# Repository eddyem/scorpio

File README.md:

# scorpio
SCORPIO control system

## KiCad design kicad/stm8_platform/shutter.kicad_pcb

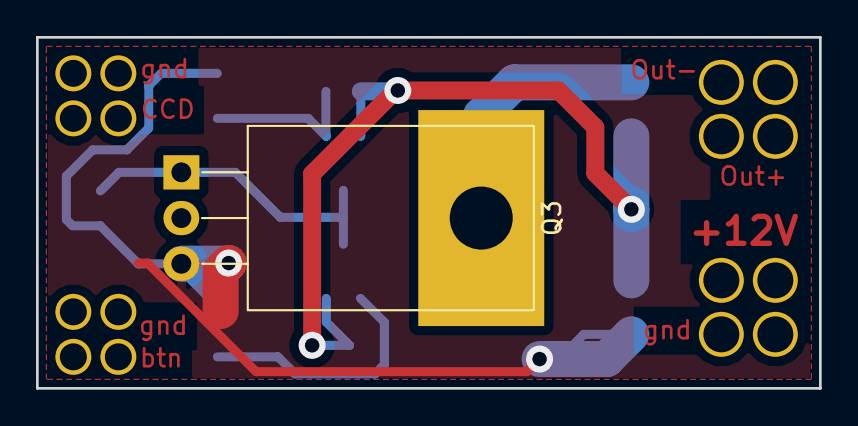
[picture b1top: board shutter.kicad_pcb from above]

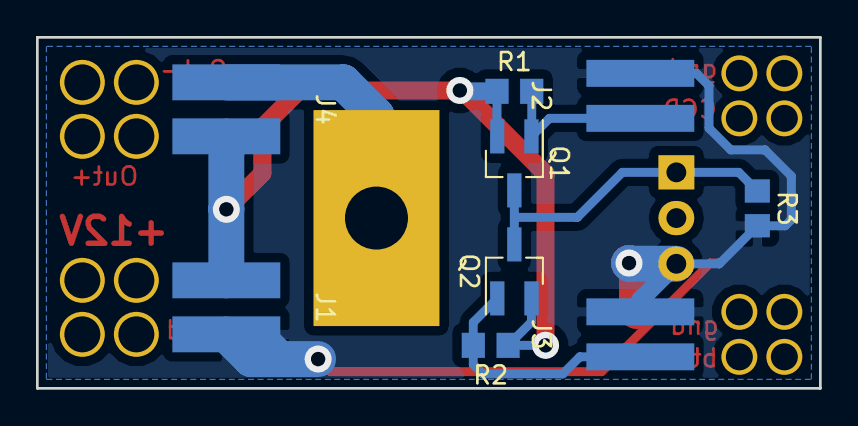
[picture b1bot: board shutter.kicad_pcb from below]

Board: 2 copper layers, 43.5 x 19.5 mm, 10 parts (9 on the bottom side), 6 nets.

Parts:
J1: Power; 2PIN_Pwr
J2: CCD; 2PIN
J3: Button; 2PIN
J4: Sutter; 2PIN_Pwr
Q1, Q2: AO3407; SOT-23_Handsoldering
Q3: IRL3303; TO-220-3_Horizontal_TabDown
R1, R2, R3: 47k; R_0805_2012Metric_Pad1.29x1.40mm_HandSolder

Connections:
+12V: J1.2, J4.1, Q1.2, Q2.2, R1.1, R2.1
GND: J1.1, J2.1, J3.1, Q3.3, R3.2
unnamed: J2.2, Q1.1, R1.2
unnamed: J3.2, Q2.1, R2.2
unnamed: J4.2, Q3.2
unnamed: Q1.3, Q2.3, Q3.1, R3.1

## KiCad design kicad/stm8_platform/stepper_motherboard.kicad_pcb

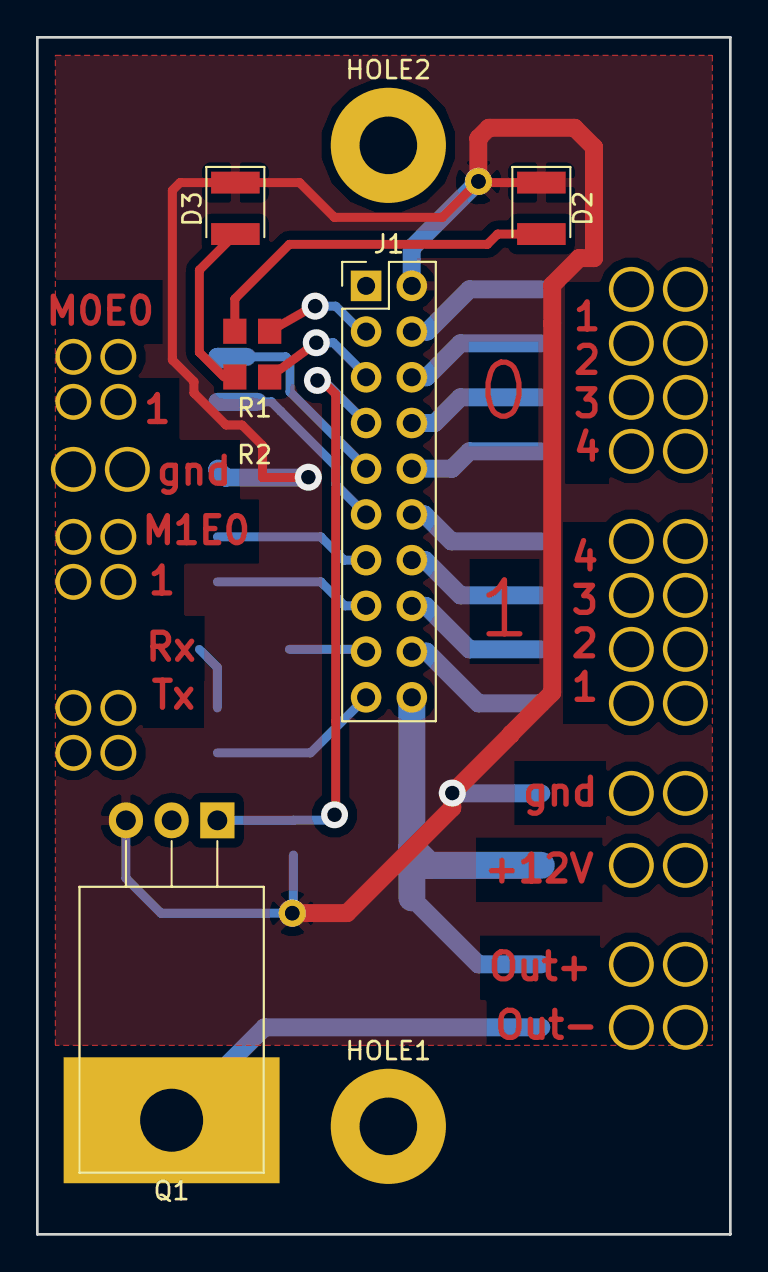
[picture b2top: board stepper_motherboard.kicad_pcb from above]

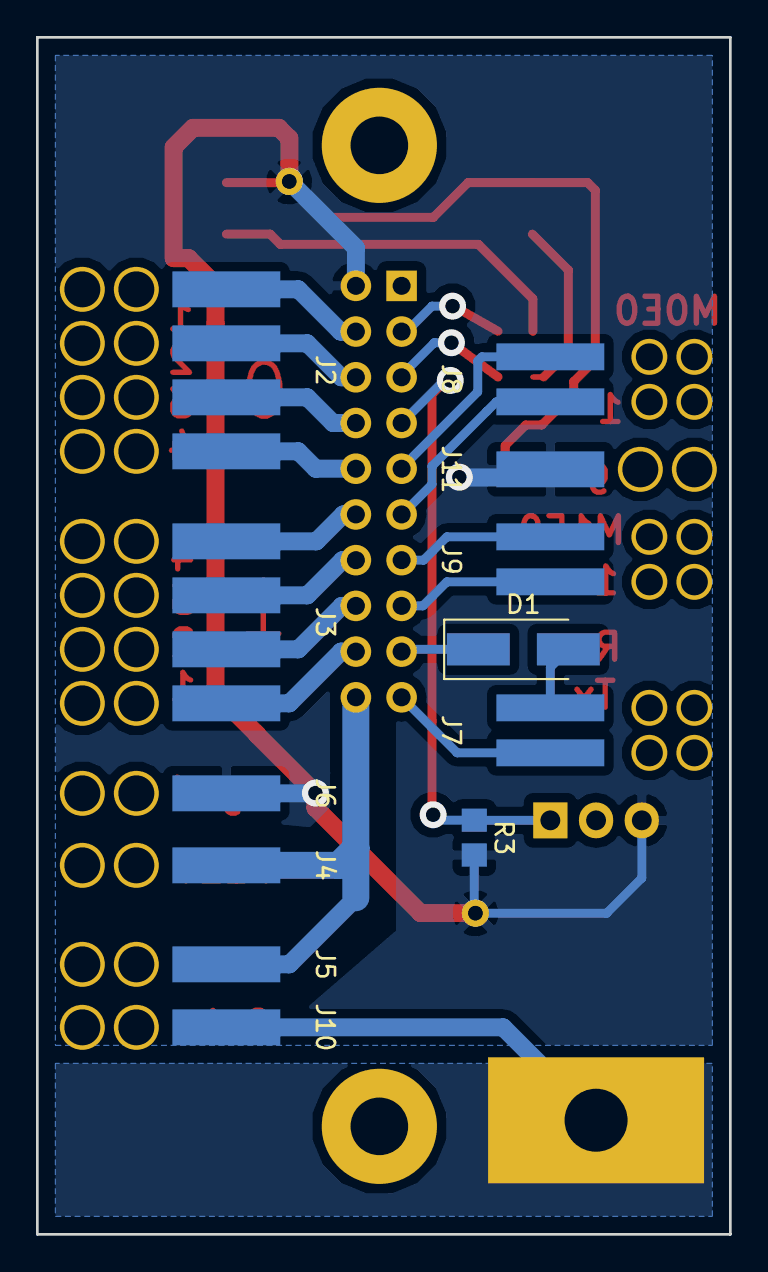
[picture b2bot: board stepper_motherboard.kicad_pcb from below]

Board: 2 copper layers, 38.5 x 66.5 mm, 20 parts (12 on the bottom side), 23 nets.

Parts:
D1: SS14; D_SMA_Handsoldering
D2, D3: LED; LED_1210_3225Metric_Pad1.22x2.70mm_HandSolder
HOLE1, HOLE2: HOLE; MountingHole_3.2mm_M3_Pad
J1: CONN_02X10; PinHeader_2x10_P2.54mm_Vertical
J2: Motor1; 4PIN
J3: Motor2; 4PIN
J4: 12V; 1PIN
J5: Load_12V; 1PIN
J6: GND; 1PIN
J7: UART; 2PIN
J8: Esw0; 2PIN
J9: Esw1; 2PIN
J10: Load_GND; 1PIN
J11: ESW_GND; 1PIN
Q1: IRL3303; TO-220-3_Horizontal_TabDown
R1, R2: 47; R_0805_2012Metric_Pad1.29x1.40mm_HandSolder
R3: 10k; R_0805_2012Metric_Pad1.29x1.40mm_HandSolder

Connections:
/M1E1: J1.9, J8.1
/M1E2: J1.11, J8.2
/M2E1: J1.13, J9.1
/M2E2: J1.15, J9.2
/OUT1: J1.3, R1.1
/OUT2: J1.5, R2.1
/OUT3: J1.7, Q1.1, R3.1
/RXD: J1.19, J7.2
/S0P1: J1.4, J2.4
/S0P2: J1.6, J2.3
/S0P3: J1.8, J2.2
/S0P4: J1.10, J2.1
/S1P1: J1.18, J3.1
/S1P2: J1.16, J3.2
/S1P3: J1.14, J3.3
/S1P4: J1.12, J3.4
/TXD: D1.1, J1.17
GND: D2.1, D3.1, J1.2, J6.1, J11.1, Q1.3, R3.2
unnamed: D1.2, J7.1
unnamed: D2.2, R1.2
unnamed: D3.2, R2.2
unnamed: J1.20, J4.1, J5.1
unnamed: J10.1, Q1.2

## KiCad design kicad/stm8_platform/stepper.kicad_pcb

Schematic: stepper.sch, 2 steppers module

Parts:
C1: 1u; C_0805_HandSoldering
C2, C3, C5: 0.1; C_0805_HandSoldering
C4: 47u; CP_Tantalum_Case-C_EIA-6032-28_Hand
D1: LED; LED_0805
D2: SP0504BAHT; SOT-23-5_HandSoldering
HOLE1, HOLE2: HOLE; hole_3mm
J1: CONN_02X10; Pin_header_2x10_side
P1: UART; Pin_Header_Angled_1x04_Pitch2.54mm
P2: SWIM; PinHeader_1x03_P2.54mm_Horizontal
Q1, Q2, Q3: AO3401; SOT-23_Handsoldering
R1, R4, R5, R12, R13, R14, R15: 10k; R_0805_HandSoldering
R2: 470; R_0805_HandSoldering
R3, R6, R7: 330; R_0805_HandSoldering
R8, R9, R10, R11: 220; R_0805_HandSoldering
SW1: SW_DIP_x03; DIP-6_W7.62mm
U1: STM8S105K4T6C; LQFP-32_7x7mm_Pitch0.8mm
U2: ULN2803A; SOIC-18W_7.5x11.6mm_Pitch1.27mm
U3: LD1117S50CTR; SOT-223

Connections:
+5V: C2.2, C4.1, D1.1, P1.1, Q1.2, Q2.2, Q3.2, R1.1, R4.1, R5.1, R12.2, SW1.1, SW1.2, SW1.3, U1.6, U1.7, U1.9, U3.2, U3.4
+12V: C3.1, J1.19, U2.10, U3.3
/M1E1: J1.10, R8.2
/M1E2: J1.12, R9.2
/M2E1: J1.14, R10.2
/M2E2: J1.16, R11.2
/NRST: C5.1, P2.1, R12.1, U1.1
/OUT1: J1.4, Q2.3
/OUT2: J1.6, Q1.3
/OUT3: J1.8, Q3.3
/PB0: U1.16, U2.1
/PB1: U1.15, U2.2
/PB2: U1.14, U2.3
/PB3: U1.13, U2.4
/PB4: D2.4, R8.1, U1.12
/PB5: D2.5, R9.1, U1.11
/PC1: R4.2, R6.2, U1.18
/PC2: R1.2, R3.2, U1.19
/PC3: R5.2, R7.2, U1.20
/PC4: R2.2, U1.21
/PC5: R15.2, SW1.6, U1.22
/PC6: R14.2, SW1.5, U1.23
/PC7: R13.2, SW1.4, U1.24
/PD0: U1.25, U2.8
/PD2: U1.27, U2.6
/PD3: U1.28, U2.5
/PD4: D2.3, R11.1, U1.29
/PD5: J1.18, P1.3, U1.30
/PD6: J1.20, P1.2, U1.31
/PD7: D2.1, R10.1, U1.32
/S1P1: J1.3, U2.18
/S1P2: J1.5, U2.17
/S1P3: J1.7, U2.16
/S1P4: J1.9, U2.15
/S2P1: J1.11, U2.14
/S2P2: J1.13, U2.13
/S2P3: J1.15, U2.12
/S2P4: J1.17, U2.11
/SWIM/PD1: P2.2, U1.26, U2.7
GND: C1.1, C2.1, C3.2, C4.2, C5.2, D2.2, J1.1, P1.4, P2.3, R13.1, R14.1, R15.1, U1.4, U1.10, U2.9, U3.1
unnamed: C1.2, U1.5
unnamed: D1.2, R2.1
unnamed: Q1.1, R3.1
unnamed: Q2.1, R6.1
unnamed: Q3.1, R7.1

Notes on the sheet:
Address
On-board LED
PWM/power outputs
SWIM
Power
ext USART
Stepper interface
ESW protection
<- P-channel ->

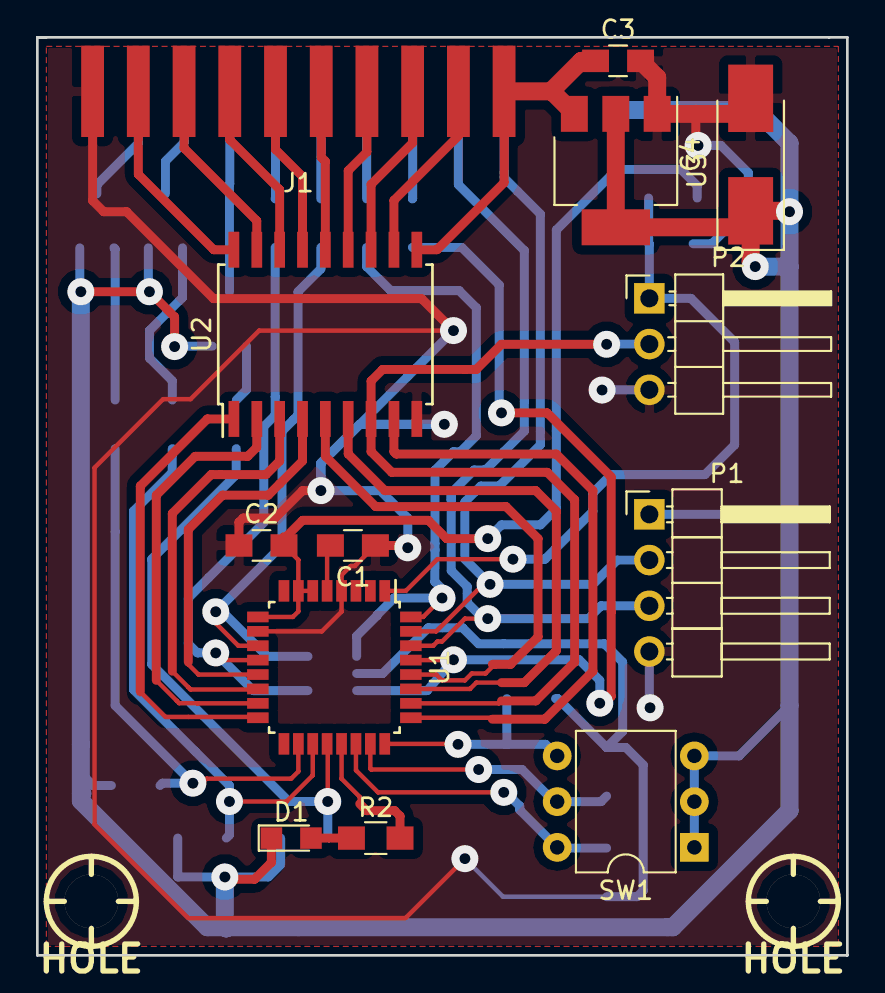
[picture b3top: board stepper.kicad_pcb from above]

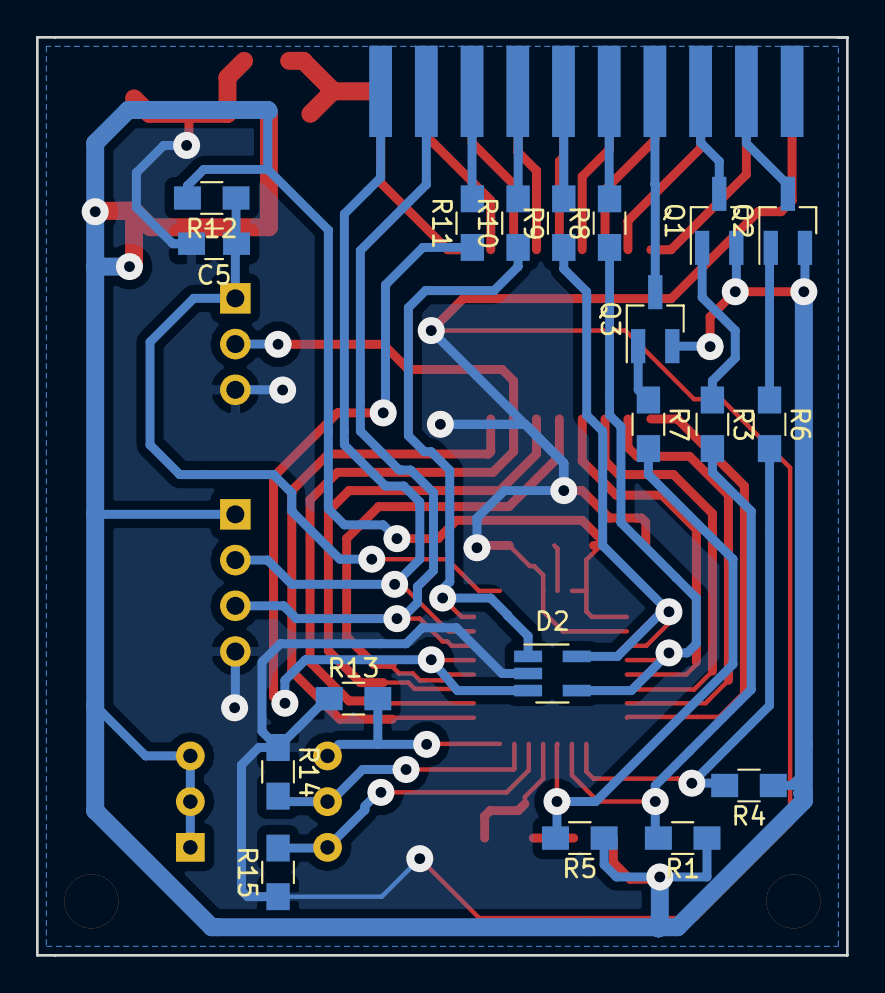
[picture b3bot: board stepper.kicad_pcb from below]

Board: 2 copper layers, 45.0 x 51.0 mm, 34 parts (19 on the bottom side), 45 nets.

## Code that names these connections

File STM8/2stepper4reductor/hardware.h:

/*
 * hardware.h - definition of ports pins & so on
 *
 * Copyright 2018 Edward V. Emelianov <eddy@sao.ru, edward.emelianoff@gmail.com>
 *
 * This program is free software; you can redistribute it and/or modify
 * it under the terms of the GNU General Public License as published by
 * the Free Software Foundation; either version 2 of the License, or
 * (at your option) any later version.
 *
 * This program is distributed in the hope that it will be useful,
 * but WITHOUT ANY WARRANTY; without even the implied warranty of
 * MERCHANTABILITY or FITNESS FOR A PARTICULAR PURPOSE.  See the
 * GNU General Public License for more details.
 *
 * You should have received a copy of the GNU General Public License
 * along with this program; if not, write to the Free Software
 * Foundation, Inc., 51 Franklin Street, Fifth Floor, Boston,
 * MA 02110-1301, USA.
 */
#pragma once
#ifndef __HARDWARE_H__
#define __HARDWARE_H__

#include "stm8s.h"

extern volatile unsigned long Global_time; // global time in ms
extern U8 MCU_no;

// macro for using in port constructions like PORT(LED_PORT, ODR) = xx
#define FORMPORT(a, b)      a ## _ ## b
#define PORT(a, b)          FORMPORT(a , b)
#define CONCAT(a, b)        a ## b

/**
 * HW:
 * PB0-3 motor0 push-pull output
 * PB4   M0E1   pullup input
 * PB5   M0E2   pullup input
 * PC1-3 PWM    push-pull output
 * PC4 - LED    push-pull output
 * PC5-7 Addr   floating input (externall pull-down)
 * PD0-3 motor1 push-pull output
 * PD4   M1E1   pullup input
 * PD5 - Tx     open-drain output \ UART
 * PD6 - Rx     floating input    /
 * PD7   M1E2   pullup input
 */
// PWM
#define PWM_PINS        (7<<1)
// LED
#define LED_PORT        PC
#define LED_PIN         GPIO_PIN4
// Address
#define ADDR_MASK       (7<<5)
#define GET_ADDR()      ((PC_IDR & ADDR_MASK)>>5)

// UART2_TX
#define UART_PORT       PD
#define UART_TX_PIN     GPIO_PIN5

// steppers
#define STP0_PORT       PB
#define STP1_PORT       PD
#define STP_PINS        (0x0f)

// end-switches
#define M0E1_PORT       PB
#define M0E2_PORT       PB
#define M1E1_PORT       PD
#define M1E2_PORT       PD
#define M0E1_PIN        (1<<4)
#define M0E2_PIN        (1<<5)
#define M1E1_PIN        (1<<7)
#define M1E2_PIN        (1<<4)

// getters: 1 active, 0 inactive
// inverse state of LED
#define LED_NSTATE()     (PORT(LED_PORT, ODR) & LED_PIN)

// end-switches (0 - shuttered)
#define CHK_M0E1()      (0 == (PORT(M0E1_PORT, IDR) & M0E1_PIN))
#define CHK_M0E2()      (0 == (PORT(M0E2_PORT, IDR) & M0E2_PIN))
#define CHK_M1E1()      (0 == (PORT(M1E1_PORT, IDR) & M1E1_PIN))
#define CHK_M1E2()      (0 == (PORT(M1E2_PORT, IDR) & M1E2_PIN))

// setters
#define LED_OFF()       (PORT(LED_PORT, ODR) |= LED_PIN)
#define LED_ON()        (PORT(LED_PORT, ODR) &= ~LED_PIN)


// getters


void hw_init();

#endif // __HARDWARE_H__

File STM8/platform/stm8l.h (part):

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#define NOPT1       *(unsigned char*)0x4802
// alternate functions remapping
// | AFR7 | ... | AFR0 |
// AFR7 - PD4 = BEEP; AFR6 - PB4/PB5 = I2C; AFR5 - PB0..3 - TIM1
// AFR4 - PD7 = TIM1_CH4; AFR3 - PD0 = TIM1_BKIN
// AFR2 - PD0 = CLK_CCO; AFR1 - PA3 = TIM3_CH1, PD2 = TIM2_CH3
// AFR0 - PD3 = ADC_ETR
#define OPT2        *(unsigned char*)0x4803
#define NOPT2       *(unsigned char*)0x4804
// trim, watchdog
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
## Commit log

2017-06-06 test
2017-06-08 alpha version
2017-06-13 Temporary system with STM8
2017-06-15 Debugged @ breadboard
2017-06-19 Beta-version, works on telescope
2017-06-30 Fixed bug with end-switches check
2017-08-18 PCB for "laser iron"
2017-09-23 small update
2018-04-11 Add firmware for atmega8535 based driver of SCORPIO base platform module
2018-10-09 add code for STM8-based 2stepper management board
2018-10-10 Final fix, all works pretty
2018-10-10 add russian readme, save kicad files in KiCAD-5.0
2018-10-11 fixed error: STM8S have NO opendrain mode for Tx of UART!!!
2018-12-14 +motherboard

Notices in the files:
STM8/platform/stm8l.h:
Copyright 2014 Edward V. Emelianoff <eddy@sao.ru>
